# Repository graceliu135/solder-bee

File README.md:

# Solder Bee

This is a bee PCB that has eyes (LEDS) that light up in the dark and vibrates like it is flying by pressing a button that activates the motor.

## BOM
- 1 Battery Holder
- 2 LEDs
- 2 Resistors
- 1 Photoresistor
- 1 Transistor (NPN)
- 1 Push Button
- 1 DC Motor

## Screenshots

Falstad [link](https://tinyurl.com/22e5xdmn)

Designed by @graceliu135 on Slack

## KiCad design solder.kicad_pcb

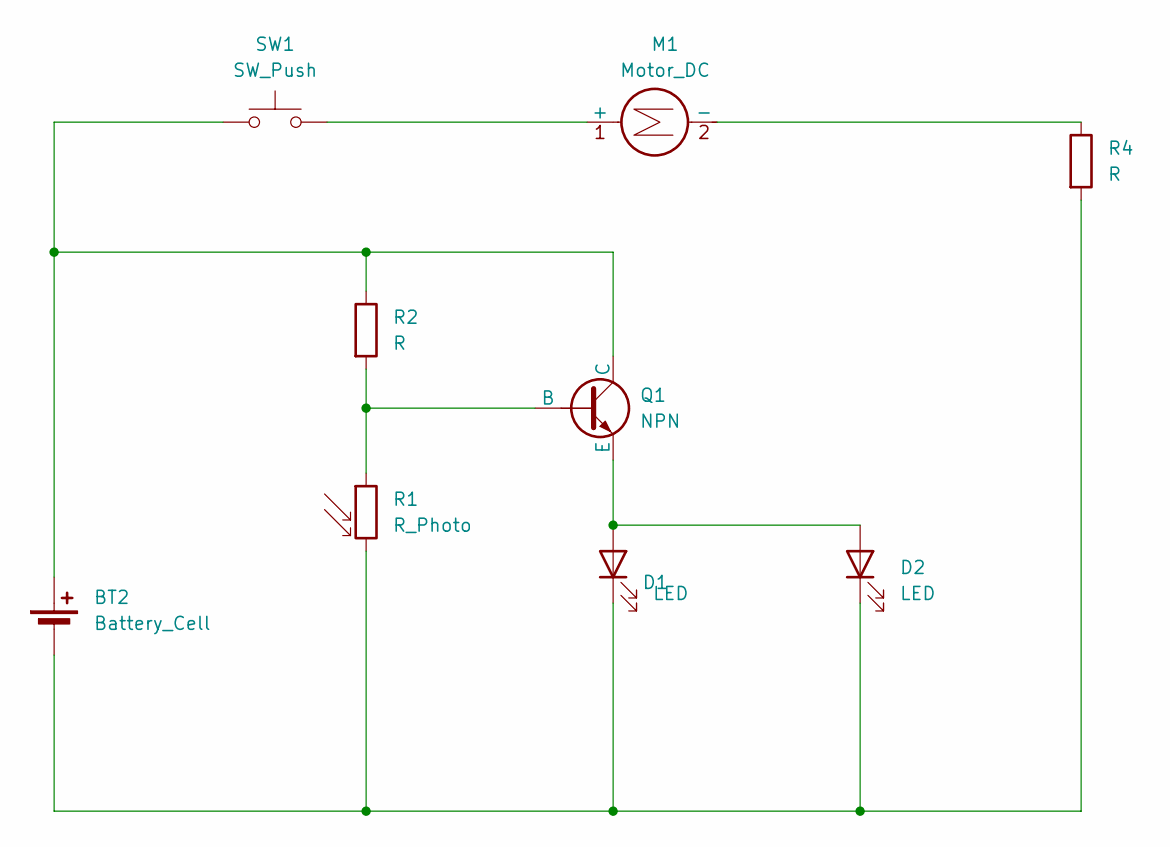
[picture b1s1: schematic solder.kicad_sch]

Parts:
BT2: Battery_Cell; BatteryHolder_Keystone_3034_1x20mm
D1, D2: LED; LED_D5.0mm
M1: Motor_DC; PinHeader_1x02_P2.54mm_Vertical
Q1: NPN; TO-92L_HandSolder
R1: R_Photo; R_LDR_5.1x4.3mm_P3.4mm_Vertical
R2, R4: R; R_Axial_DIN0207_L6.3mm_D2.5mm_P7.62mm_Horizontal
SW1: SW_Push; SW_PUSH_6mm

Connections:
unnamed: BT2.1 (+), Q1.1 (C), R2.1, SW1.1
unnamed: BT2.2 (-), D1.1 (K), D2.1 (K), R1.2, R4.2
unnamed: D1.2 (A), D2.2 (A), Q1.3 (E)
unnamed: M1.1 (+), SW1.2
unnamed: M1.2 (-), R4.1
unnamed: Q1.2 (B), R1.1, R2.2

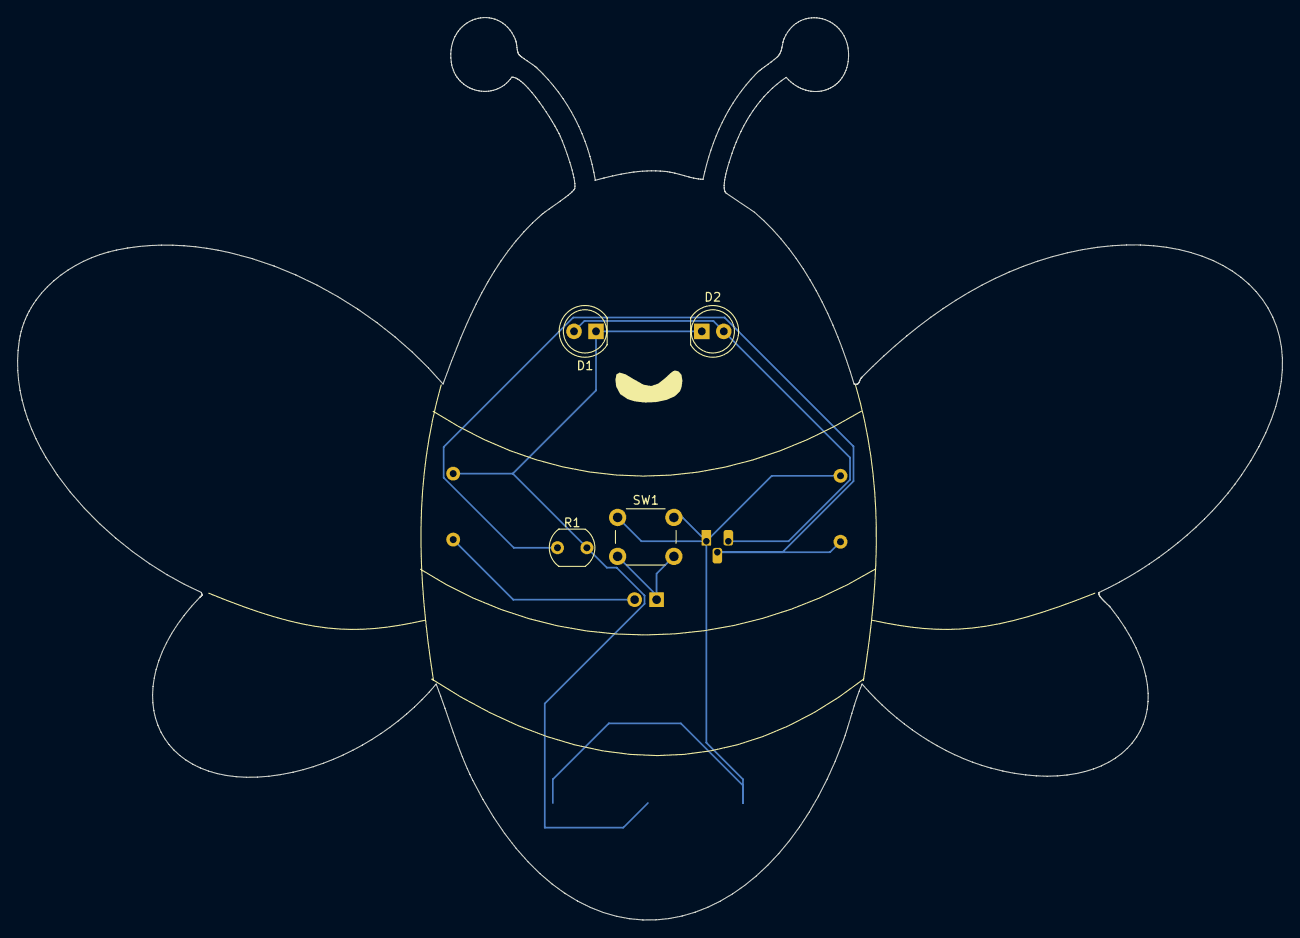
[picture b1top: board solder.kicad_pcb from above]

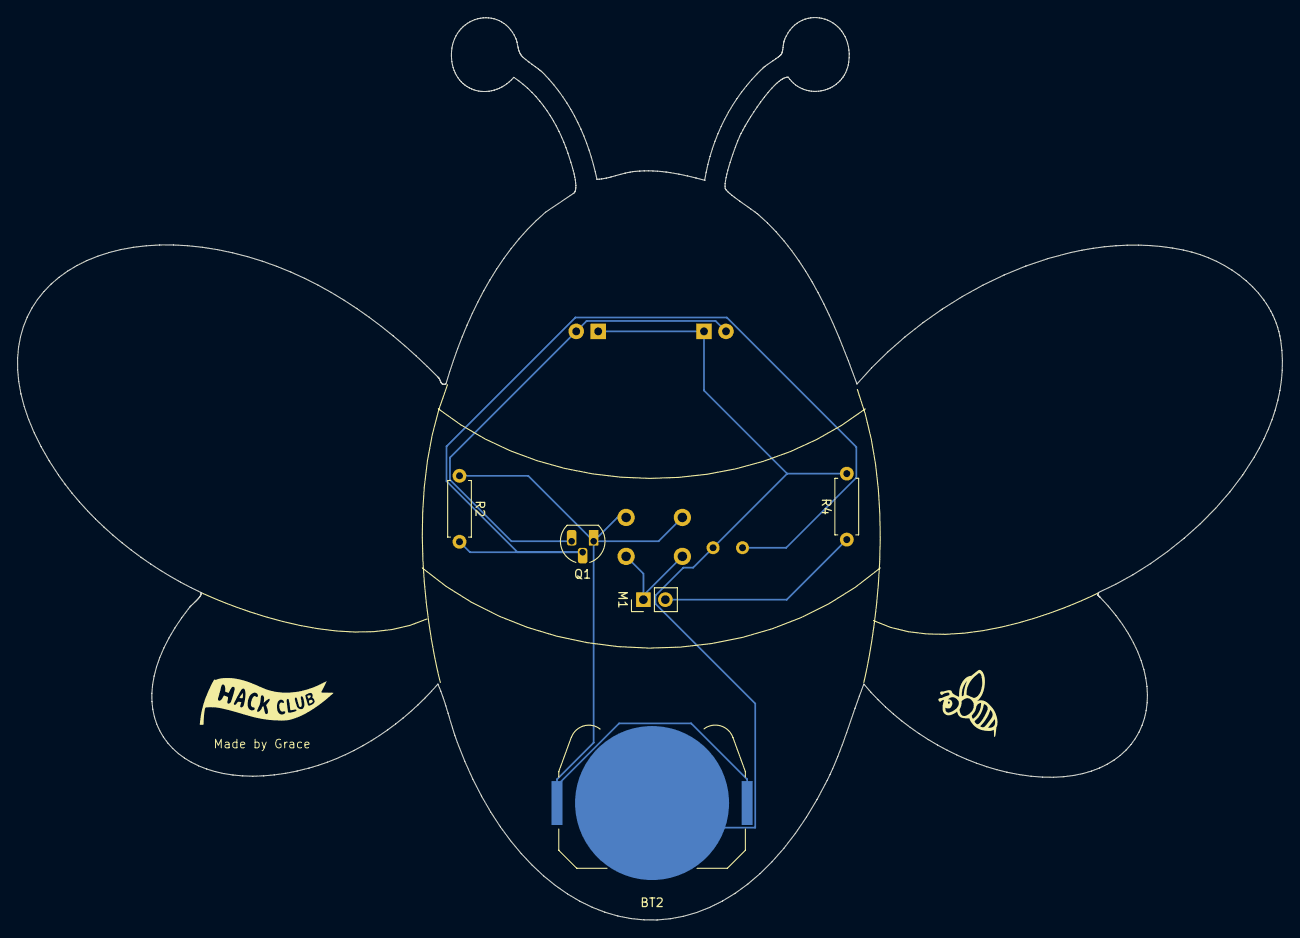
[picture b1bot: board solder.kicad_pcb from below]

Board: 2 copper layers, 146.1 x 104.3 mm, 9 parts (5 on the bottom side), 6 nets.

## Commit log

2025-06-12 Create placeholder
2025-06-13 Create production
